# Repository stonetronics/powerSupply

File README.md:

# powerSupply
voltage and current regulated power supply

this is a clone of a schematic found in an old 1982 elektor magazine + fan cooling and overtemperature protection

It uses a ua723 voltage regulator chip for voltage reference and two ua741 for voltage and current limiting and regulation
Furthermore, it is designed to either screw TO-220 transistors on the pcb to a heatsink or clamp on a completely seperate "power-transistor pack"
There can be a NTC thermistor screwed into the heatsink, which is used for fan control and overtemperature protection, which is handled by a tl084

!!Moved Mechanical to thingiverse

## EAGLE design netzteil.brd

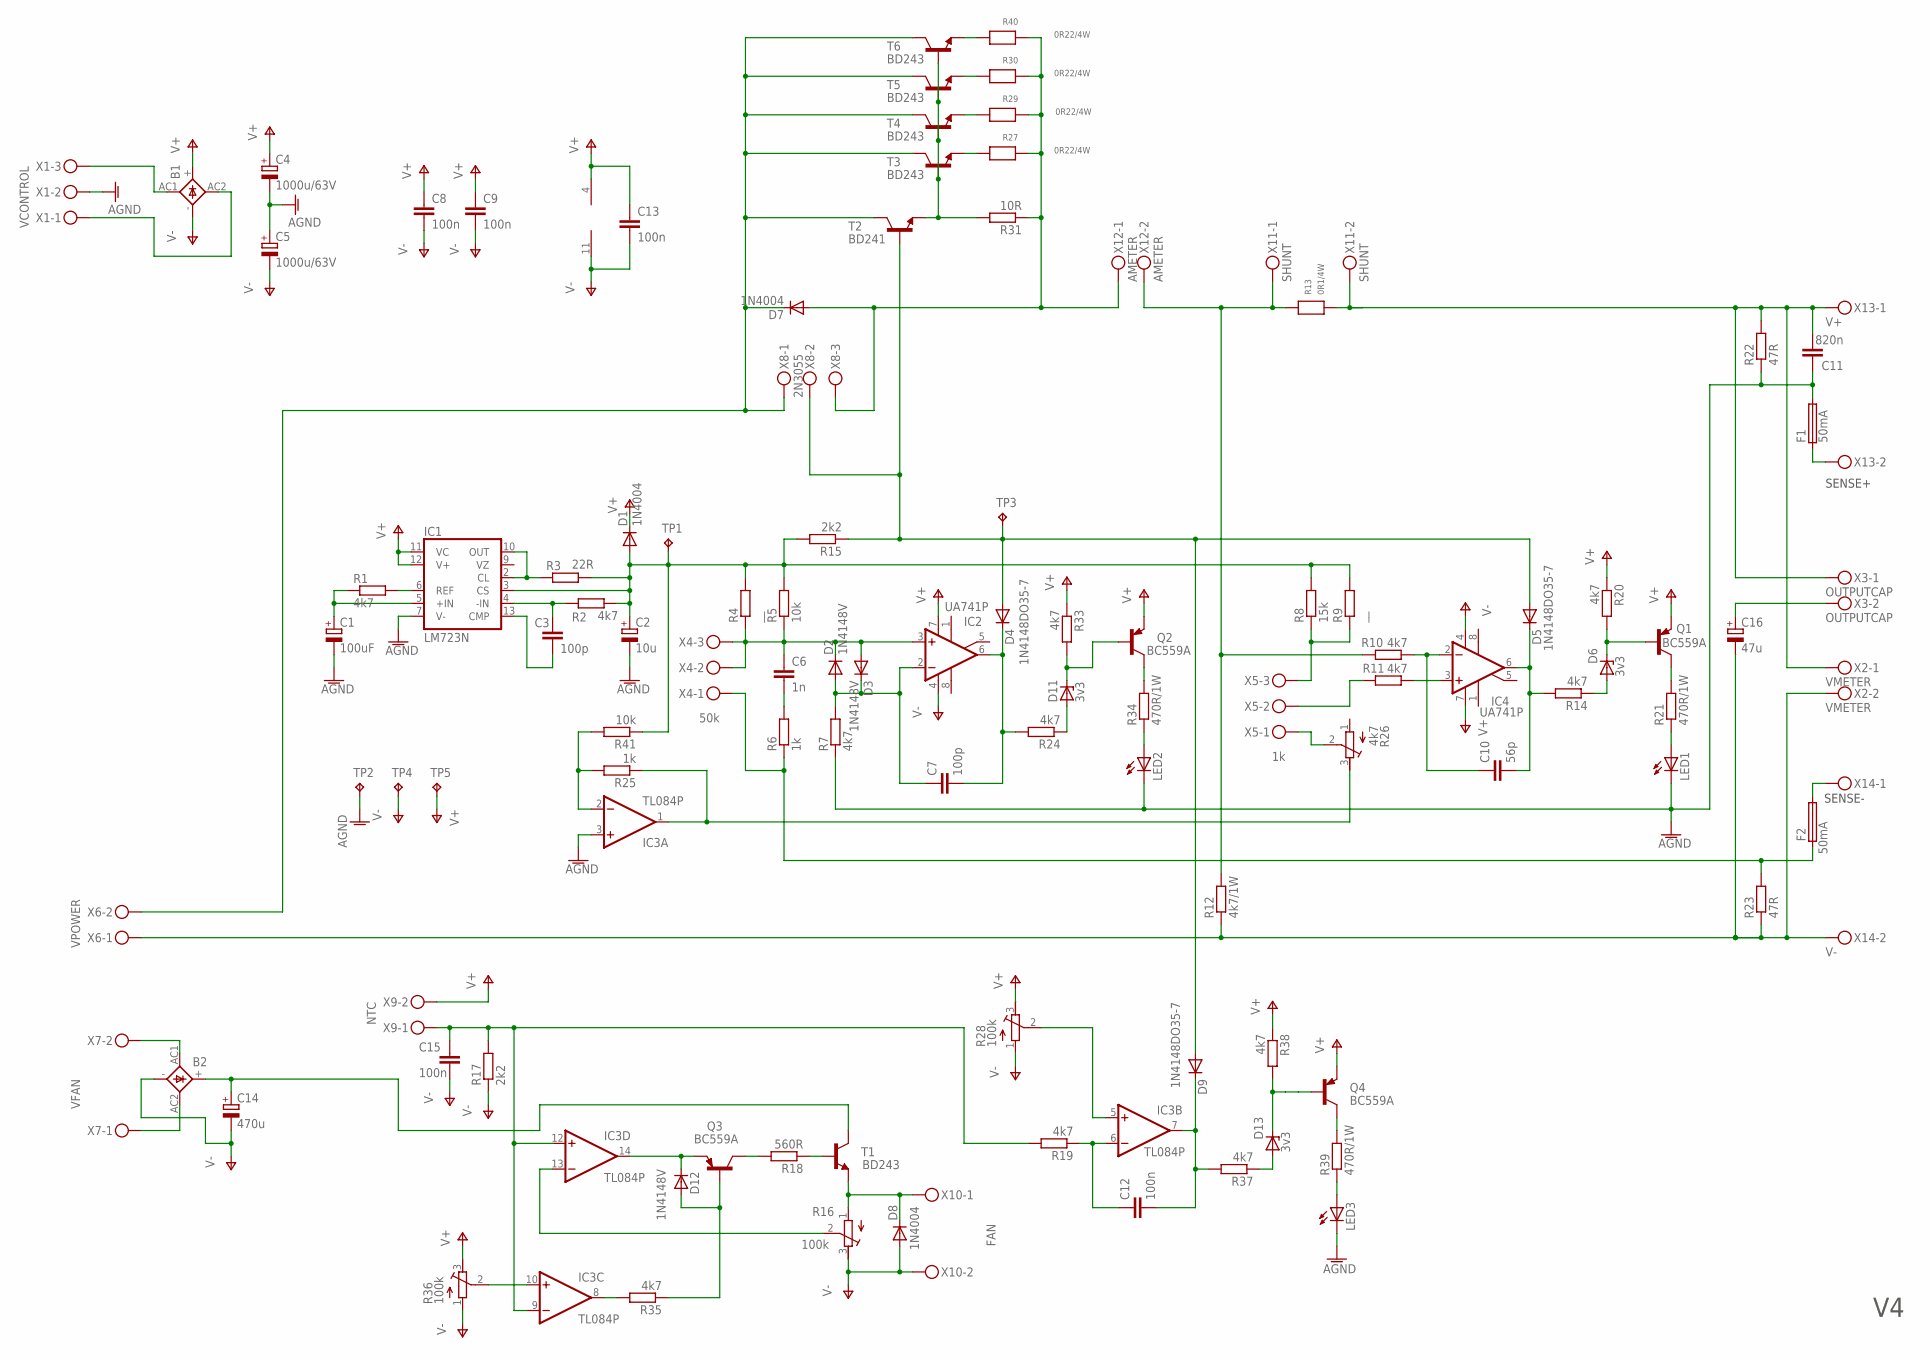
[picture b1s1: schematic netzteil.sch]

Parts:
B1, B2: 1KAB
C1: 100uF; E3,5-8
C2: 10u; E3,5-8
C3, C7: 100p; C025-025X050
C4, C5: 1000u/63V; E7,5-18
C6: 1n; C025-025X050
C8, C9, C12, C13, C15: 100n; C025-025X050
C10: 56p; C025-025X050
C11: 820n; C025-025X050
C14: 470u; E5-13
C16: 47u; E3,5-8
D1, D7, D8: 1N4004; DO41-10
D2, D3, D12: 1N4148V; SHORTDIODE
D4, D5, D9: 1N4148DO35-7; DO35-7
D6, D11, D13: 3v3; SHORTDIODE
F1, F2: 50mA; PICOFUSE
IC1: LM723N; DIL14
IC2, IC4: UA741P; DIL08
IC3: TL084P; DIL14
LED1, LED2, LED3: LED3MM
Q1, Q2, Q3, Q4: BC559A; TO92-EBC
R1, R2, R7, R10, R11, R14, R20, R24, R33, R35, R37, R38: 4k7; 0207/2V
R3: 22R; 0207/2V
R4, R9: __; 0207/2V
R5, R41: 10k; 0207/2V
R6, R25: 1k; 0207/2V
R8: 15k; 0207/2V
R12: 4k7/1W; 0207/10
R13: 0R1/4W; 4W_RM15
R15: 2k2; 0207/7
R16, R28, R36: 100k; RTRIM3296Y
R17: 2k2; 0207/2V
R18: 560R; 0207/2V
R19: 4k7; 0207/7
R21, R34, R39: 470R/1W; 0207/2V
R22, R23: 47R; 0207/2V
R26: 4k7; RTRIM3296Y
R27, R29, R30, R40: 0R22/4W; 4W_RM15
R31: 10R; 0207/2V
T1, T3, T4, T5, T6: BD243; TO220V
T2: BD241; TO220V
TP1, TP2, TP3, TP4, TP5: TPPAD1-13; P1-13
X1: VCONTROL; MKDSN1,5/3-5,08
X2: VMETER; MKDSN1,5/2-5,08
X3: OUTPUTCAP; MKDSN1,5/2-5,08
X4: 50k; MKDSN1,5/3-5,08
X5: 1k; MKDSN1,5/3-5,08
X6: VPOWER; MKDSN1,5/2-5,08
X7: VFAN; MKDSN1,5/2-5,08
X8: 2N3055; MKDSN1,5/3-5,08
X9: NTC; MKDSN1,5/2-5,08
X10: FAN; MKDSN1,5/2-5,08
X11: SHUNT; MKDSN1,5/2-5,08
X12: AMETER; MKDSN1,5/2-5,08
X13: V+; MKDSN1,5/2-5,08
X14: V-; MKDSN1,5/2-5,08

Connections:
AGND: C1.-, C2.-, C4.-, C5.+, C11.1, F1.2, IC1.7 (V-), IC3.3 (+IN), LED1.K (C), LED2.K (C), LED3.K (C), R7.1, R22.1, TP2.TP, X1.2
unnamed: IC1.6 (REF), R1.2
unnamed: C1.+, IC1.5 (+IN), R1.1
unnamed: C6.1, D2.K (C), D3.A, IC2.3 (+IN), R4.1, R5.1, X4.2, X4.3
unnamed: C6.2, R6.2
unnamed: C3.1, IC1.4 (-IN), R2.1
unnamed: IC1.2 (CL), IC1.10 (OUT), R3.1
unnamed: IC3.2 (-IN), R25.2, R41.2
unnamed: C7.1, D2.A, D3.K (C), IC2.2 (-IN), R7.2
unnamed: C3.2, IC1.13 (CMP)
unnamed: C7.2, D4.C, IC2.6 (OUT), R24.2
unnamed: C10.1, IC4.2 (-IN), R10.1
unnamed: IC4.3 (+IN), R11.1
unnamed: R8.1, R9.1, X5.3
unnamed: R11.2, X5.2
unnamed: D4.A, D5.A, D9.A, R15.1, T2.1 (B), TP3.TP, X8.2
unnamed: C10.2, D5.C, IC4.6 (OUT), R14.2
unnamed: R10.2, R12.2, R13.P$1, X11.1, X12.2
unnamed: C11.2, R13.P$2, R22.2, X2.1, X3.1, X11.2, X13.1
unnamed: D7.A, R27.P$2, R29.P$2, R30.P$2, R31.1, R40.P$2, X8.3, X12.1
unnamed: D6.K (C), Q1.B, R20.2
unnamed: D11.K (C), Q2.B, R33.2
unnamed: D11.A, R24.1
unnamed: B1.AC1, X1.3
unnamed: B1.AC2, X1.1
unnamed: Q2.C, R34.2
unnamed: D6.A, R14.1
unnamed: Q1.C, R21.2
unnamed: LED1.A, R21.1
unnamed: D7.C, T2.2 (C), T3.2 (C), T4.2 (C), T5.2 (C), T6.2 (C), X6.2, X8.1
unnamed: F2.1, R6.1, R23.2, X4.1
unnamed: C16.-, R12.1, R23.1, X2.2, X6.1, X14.2
unnamed: R26.2 (S), X5.1
unnamed: IC3.1 (OUT), R25.1, R26.3 (E)
unnamed: LED2.A, R34.1
unnamed: C16.+, X3.2
unnamed: D12.K (C), IC3.14 (OUT), Q3.E
unnamed: Q3.C, R18.2
unnamed: D12.A, Q3.B, R35.1
unnamed: IC3.8 (OUT), R35.2
unnamed: IC3.10 (+IN), R36.2 (S)
unnamed: IC3.13 (-IN), R16.2 (S)
unnamed: C12.1, IC3.6 (-IN), R19.1
unnamed: F2.2, X14.1
unnamed: R18.1, T1.1 (B)
unnamed: IC3.5 (+IN), R28.2 (S)
unnamed: D8.C, R16.1 (A), T1.3 (E), X10.1
unnamed: C12.2, D9.C, IC3.7 (OUT), R37.2
unnamed: C15.1, IC3.9 (-IN), IC3.12 (+IN), R17.2, R19.2, X9.1
unnamed: R31.2, T2.3 (E), T3.1 (B), T4.1 (B), T5.1 (B), T6.1 (B)
unnamed: R27.P$1, T3.3 (E)
unnamed: R29.P$1, T4.3 (E)
unnamed: R30.P$1, T5.3 (E)
unnamed: B2.AC1, X7.2
unnamed: B2.AC2, X7.1
unnamed: B2.+, C14.+, T1.2 (C)
unnamed: D13.K (C), Q4.B, R38.2
unnamed: D13.A, R37.1
unnamed: Q4.C, R39.2
unnamed: LED3.A, R39.1
unnamed: F1.1, X13.2
unnamed: R40.P$1, T6.3 (E)
V723: C2.+, D1.A, IC1.3 (CS), R2.2, R3.2, R4.2, R5.2, R8.2, R9.2, R15.2, R41.1, TP1.TP
V+: B1.+, C4.+, C8.1, C9.1, C13.1, D1.C, IC1.11 (VC), IC1.12 (V+), IC2.7 (V+), IC3.4 (V+), IC4.7 (V+), Q1.E, Q2.E, Q4.E, R20.1, R28.3 (E), R33.1, R36.3 (E), R38.1, TP5.TP, X9.2
V-: B1.-, B2.-, C5.-, C8.2, C9.2, C13.2, C14.-, C15.2, D8.A, IC2.4 (V-), IC3.11 (V-), IC4.4 (V-), R16.3 (E), R17.1, R28.1 (A), R36.1 (A), TP4.TP, X10.2

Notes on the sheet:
SENSE-
SENSE+

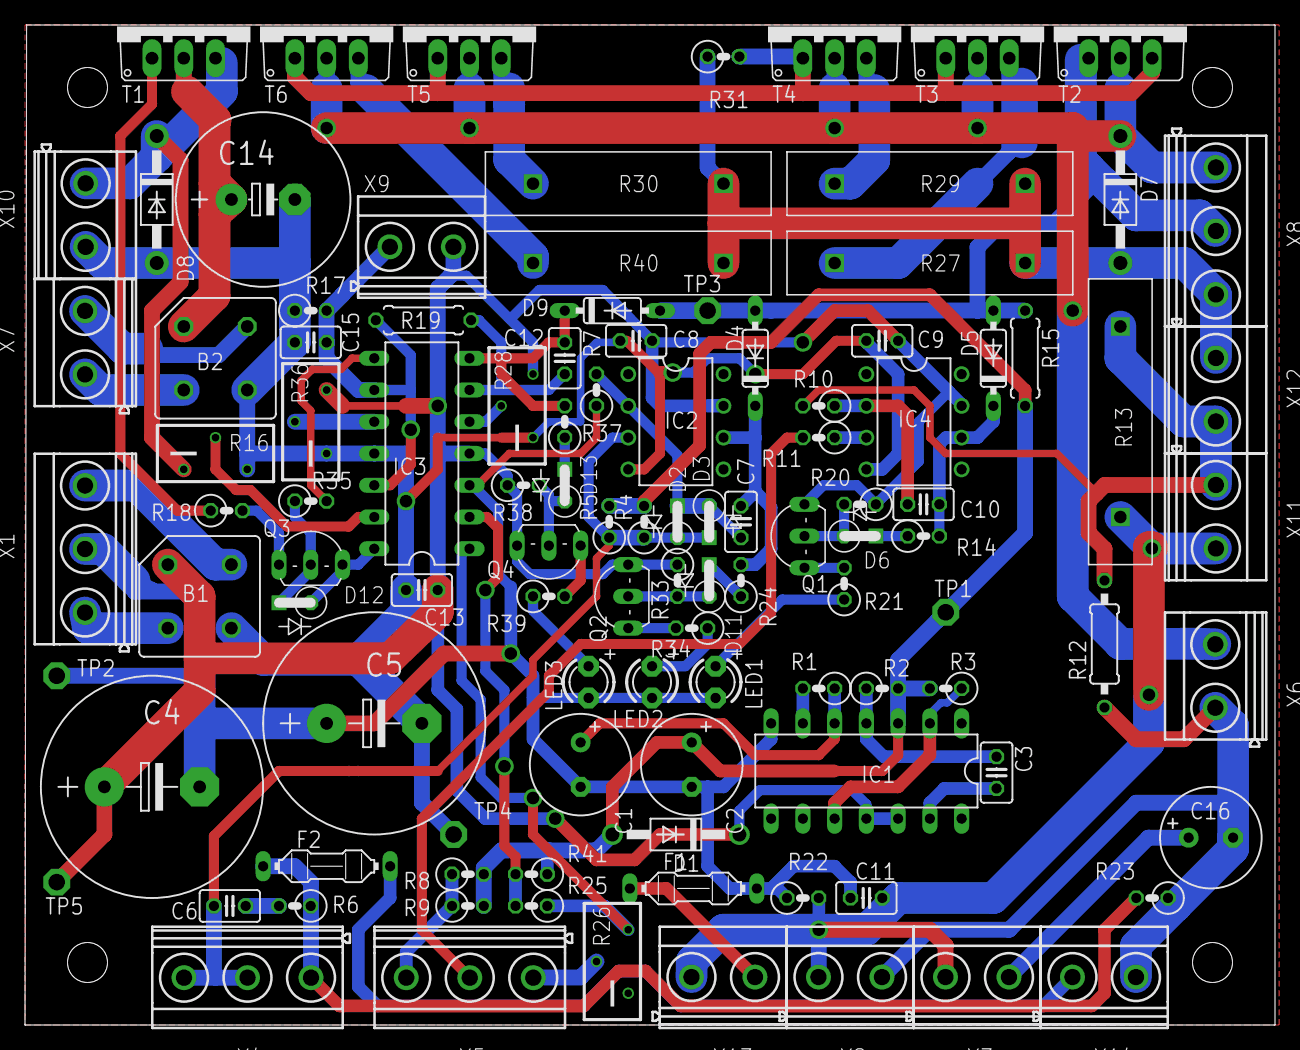
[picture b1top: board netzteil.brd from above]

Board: 2 copper layers, 100.0 x 80.0 mm, 108 parts (0 on the bottom side), 65 nets.

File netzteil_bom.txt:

Stückliste exportiert aus /home/stone/eagle/Netzteil/netzteil.sch am 02.04.18 02:46

Qty Value           Device            Package         Parts                          Description                          
1                   -NPN-TO220        TO220           T1                             NPN Transistror                      
1                   LED3MM            LED3MM          LED1                           LED                                  
1                   ZENER-DIODEDO34-7 DO34Z7          D6                             Z-Diode                              
2   100n            C-EU025-025X050   C025-025X050    C8, C9                         CAPACITOR, European symbol           
3   100p            C-EU025-025X050   C025-025X050    C3, C7, C10                    CAPACITOR, European symbol           
1   100uF           CPOL-EUE3.5-8     E3,5-8          C1                             POLARIZED CAPACITOR, European symbol 
1   10R/1W          R-EU_0411/12      0411/12         R16                            RESISTOR, European symbol            
1   10k             R-EU_0207/2V      0207/2V         R5                             RESISTOR, European symbol            
2   10k             R-TRIMM3296Y      RTRIM3296Y      R25, R26                       Trimm resistor                       
1   10u             CPOL-EUE3.5-8     E3,5-8          C2                             POLARIZED CAPACITOR, European symbol 
1   15k             R-EU_0207/2V      0207/2V         R8                             RESISTOR, European symbol            
2   1N4004          1N4004            DO41-10         D1, D7                         DIODE                                
4   1N4148DO35-7    1N4148DO35-7      DO35-7          D2, D3, D4, D5                 DIODE                                
1   1k              MKDSN1,5/3-5,08   MKDSN1,5/3-5,08 X5                             MKDSN 1,5/ 3-5,08 Printklemme        
1   1k              R-EU_0207/2V      0207/2V         R6                             RESISTOR, European symbol            
1   1n              C-EU025-025X050   C025-025X050    C6                             CAPACITOR, European symbol           
1   22R             R-EU_0207/2V      0207/2V         R3                             RESISTOR, European symbol            
3   2N3055          MKDSN1,5/3-5,08   MKDSN1,5/3-5,08 X8, X9, X10                    MKDSN 1,5/ 3-5,08 Printklemme        
1   2k2             R-EU_0207/7       0207/7          R15                            RESISTOR, European symbol            
1   470R/1W         R-EU_0207/2V      0207/2V         R21                            RESISTOR, European symbol            
1   470k            R-EU_0207/2V      0207/2V         R24                            RESISTOR, European symbol            
2   47R             R-EU_0207/2V      0207/2V         R22, R23                       RESISTOR, European symbol            
1   47u             CPOL-EUE3.5-8     E3,5-8          C16                            POLARIZED CAPACITOR, European symbol 
7   4k7             R-EU_0207/2V      0207/2V         R1, R2, R7, R10, R11, R14, R20 RESISTOR, European symbol            
1   4k7/1W          R-EU_0411/12      0411/12         R12                            RESISTOR, European symbol            
1   50k             MKDSN1,5/3-5,08   MKDSN1,5/3-5,08 X4                             MKDSN 1,5/ 3-5,08 Printklemme        
1   820n            C-EU025-025X050   C025-025X050    C11                            CAPACITOR, European symbol           
1   BC559A          BC559A            TO92-EBC        Q1                             PNP Transistror                      
1   LM723N          LM723N            DIL14           IC1                            Positive VOLTAGE REGULATOR           
2   MKDSN1,5/2-5,08 MKDSN1,5/2-5,08   MKDSN1,5/2-5,08 X2, X3                         MKDSN 1,5/ 2-5,08 Printklemme        
2   MKDSN1,5/3-5,08 MKDSN1,5/3-5,08   MKDSN1,5/3-5,08 X1, X11                        MKDSN 1,5/ 3-5,08 Printklemme        
1   POWER_KO        MKDSN1,5/2-5,08   MKDSN1,5/2-5,08 X12                            MKDSN 1,5/ 2-5,08 Printklemme        
4   R22/3W          R-EU_0411/12      0411/12         R13, R17, R18, R19             RESISTOR, European symbol            
1   STROMMESSUNG    MKDSN1,5/2-5,08   MKDSN1,5/2-5,08 X7                             MKDSN 1,5/ 2-5,08 Printklemme        
1   TL072P          TL072P            DIL08           IC2                            OP AMP                               
1   V+              MKDSN1,5/2-5,08   MKDSN1,5/2-5,08 X13                            MKDSN 1,5/ 2-5,08 Printklemme        
1   V-              MKDSN1,5/2-5,08   MKDSN1,5/2-5,08 X14                            MKDSN 1,5/ 2-5,08 Printklemme        
2   __              R-EU_0207/2V      0207/2V         R4, R9                         RESISTOR, European symbol

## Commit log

2018-04-02 initial commit schematics and board
2018-05-02 added minimum temperature enable for fan, fixed errors in regulation, adapted clamps for panel meters, added C.V. and overtemperature display diode, seperate supply for fan
2018-05-13 added amperemeter and shunt clamps, semi-final version of the schematic for the pcb
2018-05-13 repair commit
2018-05-15 finished pre-final pcb layout
2018-05-22 started housing for prototype 1
2018-05-23 work on housing for prototype 1
2018-05-24 almost finished housing for prototype 1
2019-03-29 moved mechanical to thingiverse
